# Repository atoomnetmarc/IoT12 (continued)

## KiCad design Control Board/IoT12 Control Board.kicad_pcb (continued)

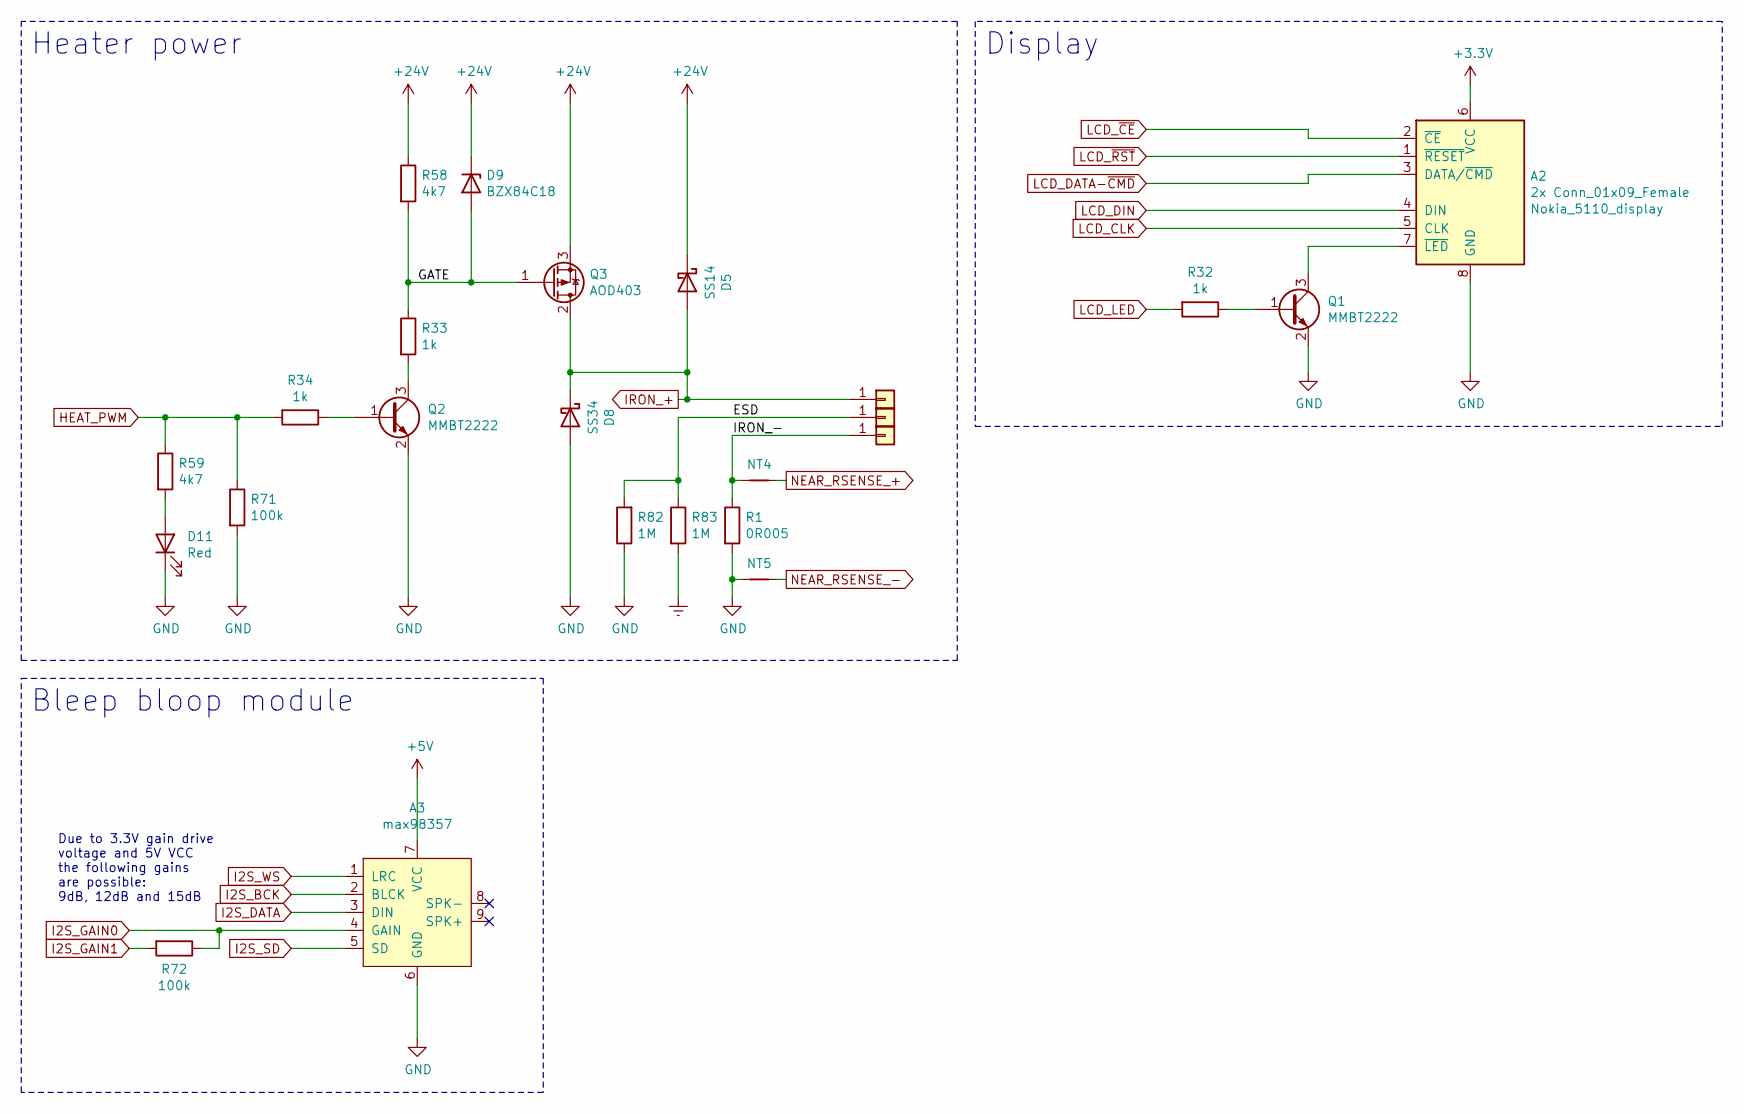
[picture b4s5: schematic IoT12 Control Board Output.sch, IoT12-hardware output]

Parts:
A2: 2x Conn_01x09_Female; Nokia_5110_display_module
A3: max98357
D5: SS14; D_SMA
D8: SS34; D_SMA
D9: BZX84C18; D_SOT-23_ANK
D11: Red; LED_0805_2012Metric_Pad1.15x1.40mm_HandSolder
J3, J4, J5: TestPoint_THTPad_D2.0mm_Drill1.0mm
NT4, NT5: NetTie-2_SMD_Pad0.25mm
Q1, Q2: MMBT2222; SOT-23
Q3: AOD403; TO-252-2
R1: 0R005; R_2512_6332Metric_Pad1.52x3.35mm_HandSolder
R32, R33, R34: 1k; R_0805_2012Metric_Pad1.20x1.40mm_HandSolder
R58, R59: 4k7; R_0805_2012Metric_Pad1.20x1.40mm_HandSolder
R71, R72: 100k; R_0805_2012Metric_Pad1.20x1.40mm_HandSolder
R82, R83: 1M; R_0805_2012Metric_Pad1.20x1.40mm_HandSolder

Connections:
+5V: A3.7 (VCC); also elsewhere on the board
+24V: D5.1 (K), D9.1 (K), Q3.3 (S), R58.1; also elsewhere on the board
/Output/ESD: J3.1, R82.2, R83.1
/Output/GATE: D9.2 (A), Q3.1 (G), R33.1, R58.2
/Output/IRON_-: J4.1, NT4.1, R1.1
Earth: R83.2; also elsewhere on the board
GND: A2.8 (GND), A3.6 (GND), D8.2 (A), D11.1 (K), NT5.1, Q1.2 (E), Q2.2 (E), R1.2, R71.2, R82.1; also elsewhere on the board
HEAT_PWM: R34.2, R59.1, R71.1; also elsewhere on the board
I2S_BCK: A3.2 (BLCK); also elsewhere on the board
I2S_DATA: A3.3 (DIN); also elsewhere on the board
I2S_GAIN0: A3.4 (GAIN), R72.1; also elsewhere on the board
I2S_GAIN1: R72.2; also elsewhere on the board
I2S_SD: A3.5 (SD); also elsewhere on the board
I2S_WS: A3.1 (LRC); also elsewhere on the board
IRON_+: D5.2 (A), D8.1 (K), J5.1, Q3.2 (D); also elsewhere on the board
LCD_CLK: A2.5 (CLK); also elsewhere on the board
LCD_DATA-~CMD: A2.3 (DATA/~CMD); also elsewhere on the board
LCD_DIN: A2.4 (DIN); also elsewhere on the board
LCD_LED: R32.2; also elsewhere on the board
LCD_~CE: A2.2 (~CE); also elsewhere on the board
LCD_~RST: A2.1 (~RESET); also elsewhere on the board
NEAR_RSENSE_+: NT4.2; also elsewhere on the board
NEAR_RSENSE_-: NT5.2; also elsewhere on the board
unnamed: A2.7 (~LED), Q1.3 (C)
unnamed: D11.2 (A), R59.2
unnamed: Q1.1 (B), R32.1
unnamed: Q2.1 (B), R34.1
unnamed: Q2.3 (C), R33.2

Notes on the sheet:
Display
Heater power
Bleep bloop module
Due to 3.3V gain drive voltage and 5V VCC the following gains are possible: 9dB, 12dB and 15dB

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
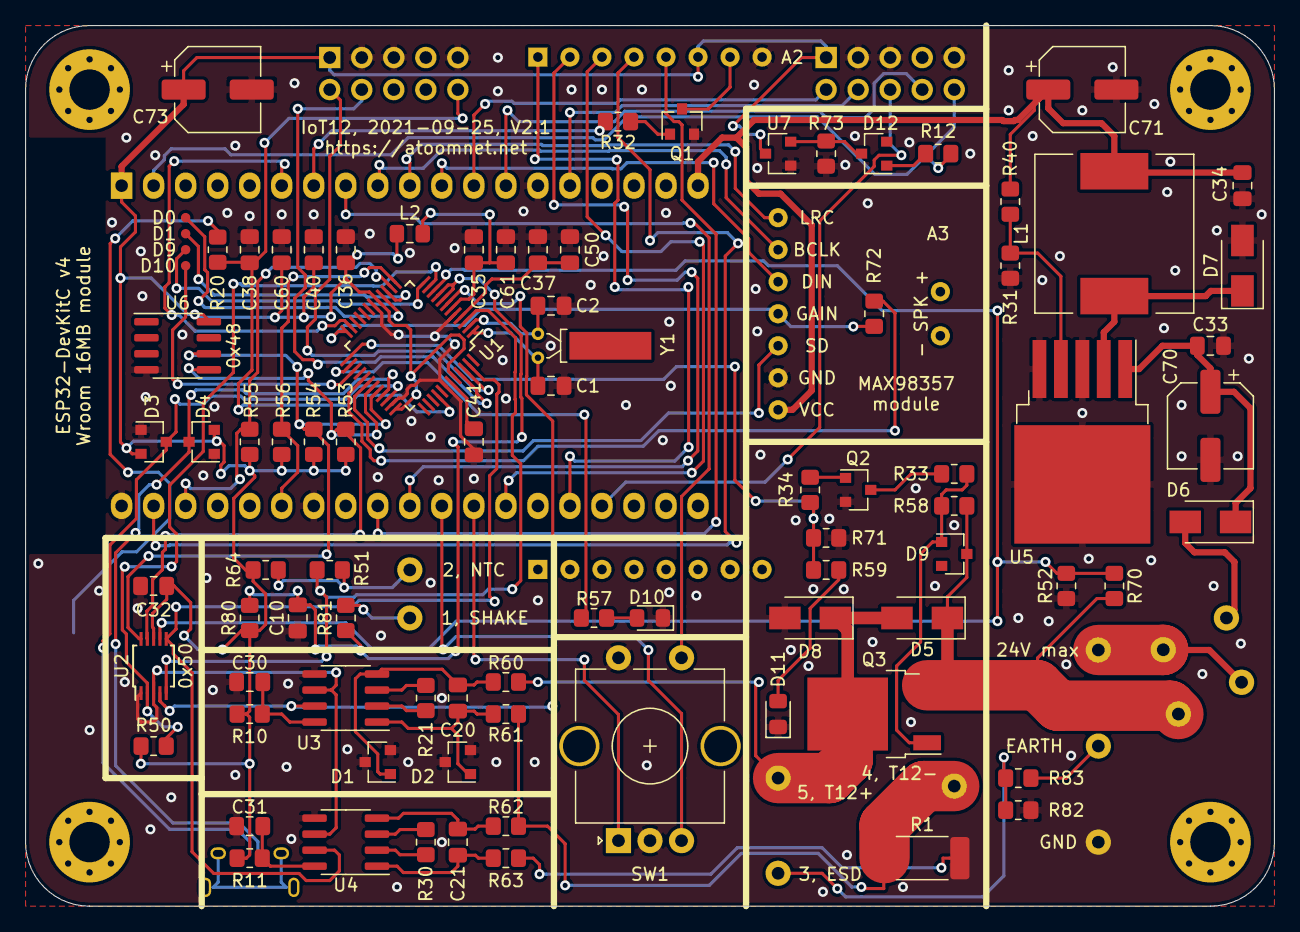
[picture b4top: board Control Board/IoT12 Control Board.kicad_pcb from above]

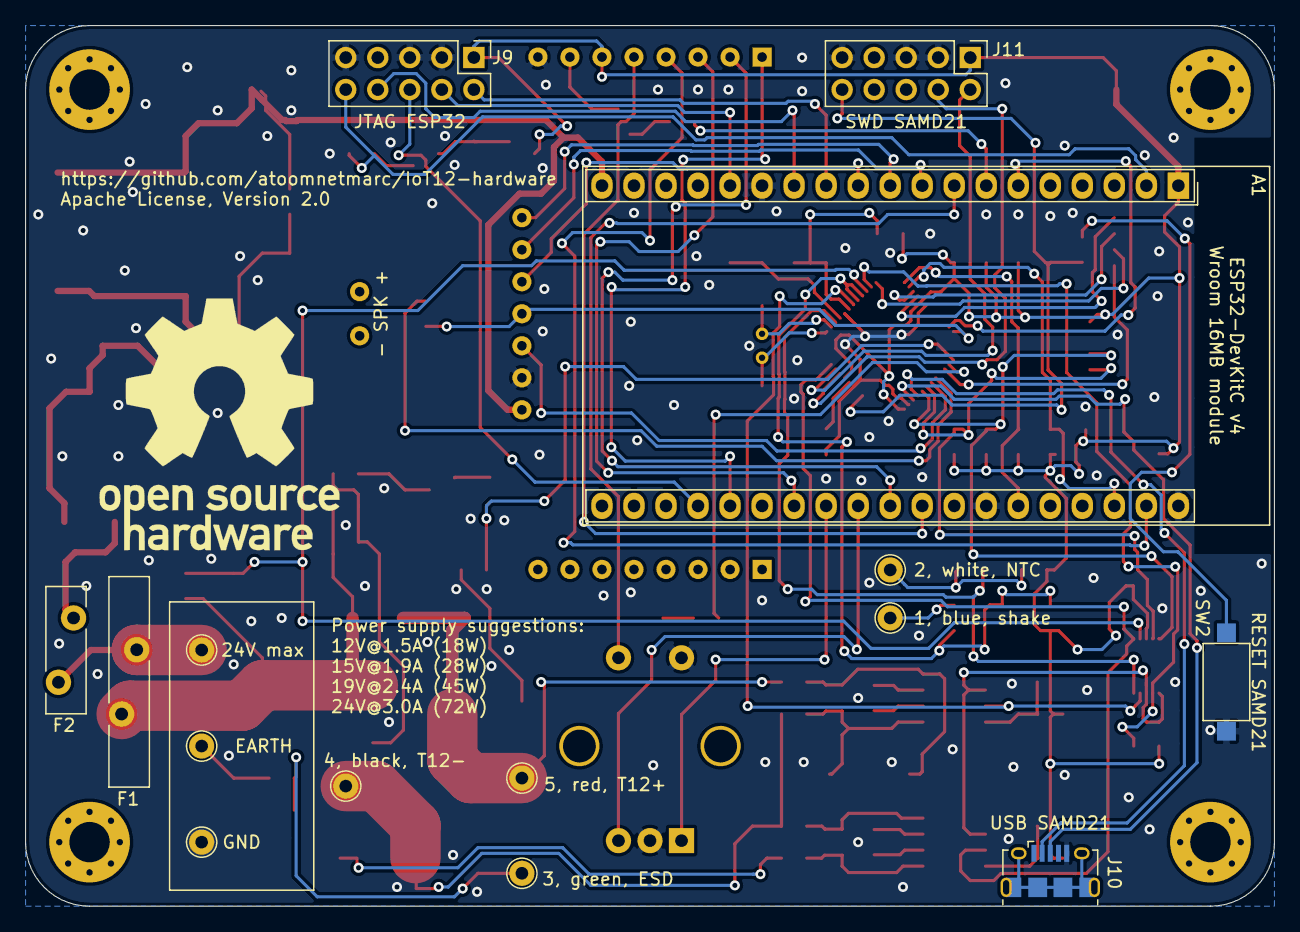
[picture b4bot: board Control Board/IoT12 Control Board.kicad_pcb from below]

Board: 2 copper layers, 99.1 x 69.8 mm, 111 parts (15 on the bottom side), 85 nets.

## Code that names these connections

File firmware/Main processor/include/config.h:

/*
 *
 * Copyright Marc Ketel
 * SPDX-License-Identifier: Apache-2.0
 *
 */

#pragma once

#define PIN_HEAT_INT 35

#define PIN_I2S_CLK   25
#define PIN_I2S_WS    26
#define PIN_I2S_DATA  27
#define PIN_I2S_SD    33
#define PIN_I2S_GAIN0 13
#define PIN_I2S_GAIN1 14

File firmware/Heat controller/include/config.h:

/*
 *
 * Copyright Marc Ketel
 * SPDX-License-Identifier: Apache-2.0
 *
 */

#pragma once

#include <Arduino.h>

#define PIN_HEAT_PWM  (10u)
#define PIN_24V_ON    (9u)
#define PIN_ADC_READY (8u)
#define PIN_HEAT_INT  (4u)
#define PIN_FLASH_CS  (6u)
#define PIN_SHAKE     A3

#define PIN_INTERNAL_ADC_NTC          PIN_A0
#define PIN_INTERNAL_ADC_TEMP         PIN_A1
#define PIN_INTERNAL_ADC_VIN          PIN_A4
#define PIN_INTERNAL_ADC_IRON_CURRENT PIN_A5

#define AIN_EXTERNAL_ADC_TEMP         (0u)
#define AIN_EXTERNAL_ADC_NTC          (1u)
#define AIN_EXTERNAL_ADC_IRON_CURRENT (2u)
#define AIN_EXTERNAL_ADC_VIN          (3u)

#define I2C_ADDRESS_ADS1115 0x48

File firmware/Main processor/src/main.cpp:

/*
 *
 * Copyright Marc Ketel
 * SPDX-License-Identifier: Apache-2.0
 *
 */

#include <esp32-hal-cpu.h>

#include <Wire.h>

#include <IoAbstraction.h>
#include <TaskManagerIO.h>

#include "HeatController.h"
#include "config.h"
#include "display.h"
#include "main.h"
#include "webserverc.h"
#include "wific.h"

volatile int encoderValue = 30;
void onEncoderChange(int newValue) {
    RequestDrawDisplay();

    if (newValue > 0 && encoderValue < 600) {
        encoderValue += 5;
    }

    if (newValue < 0 && encoderValue > -10) {
        encoderValue -= 5;
    }

    /*
    if (newValue < 0)
        Serial.println("down");
    else
        Serial.println("up");
    */

    float celsius = encoderValue;

    HeatController.setTargetTemperature(celsius + 273.15f);
}

void onSpinwheelClicked(uint8_t pin, bool heldDown) {
    Serial.print("Button pressed ");
    Serial.println(heldDown ? "Held" : "Pressed");

    /*
  u8g2.beginSimple();
  u8g2.setPowerSave(0);
  */

    if (heldDown == false) {
        HEATER_STATE state = HeatController.getHeaterState();
        if (state == HEATER_STATE::OFF) {
            HeatController.setHeaterState(HEATER_STATE::ON);
        } else {
            HeatController.setHeaterState(HEATER_STATE::OFF);
        }
    }

    /*
    SerialNumber_t sn = HeatController.getSerialNumber();
    Serial.println(String("Serial number heatcontroller: ") + String(sn.word0, HEX) + String(" ") + String(sn.word1, HEX) + String(" ") + String(sn.word2, HEX) + String(" ") + String(sn.word3, HEX) );

    uint16_t const1 = HeatController.getConst1();
    Serial.println(String("Const1 heatcontroller: 0x") + String(const1, HEX) );

    float const2 = HeatController.getConst2();
    Serial.println(String("Const2 heatcontroller: ") + String(const2, 6));
    */
}

void setup() {
    Wire.begin(SDA, SCL, 100000U);

    Serial.begin(115200);
    Serial.println(F("Booting"));

    setCpuFrequencyMhz(80);
    Serial.println(String(F("CPU freq: ")) + String(ESP.getCpuFreqMHz()) + String(F("MHz")));
    Serial.println(String(F("Flash size: ")) + String(ESP.getFlashChipSize() / 1024 / 1024) + String(F("MiB")));

    DisplaySetup();

    pinMode(PIN_ROT_A, PULLUP);
    pinMode(PIN_ROT_B, PULLUP);
    pinMode(PIN_ROT_SW, PULLUP);
    switches.initialiseInterrupt(ioUsingArduino(), true);
    switches.addSwitch(PIN_ROT_SW, onSpinwheelClicked);
    setupRotaryEncoderWithInterrupt(PIN_ROT_A, PIN_ROT_B, onEncoderChange);
    switches.changeEncoderPrecision(0, 0);

    WificSetup();

    pinMode(PIN_LCD_LED, OUTPUT);
    digitalWrite(PIN_LCD_LED, 1);

    if (HeatController.init() == false) {
        Serial.println(F("Heat controller not compatible"));
    }
    Serial.println(String(F("Heat controller version: ")) + HeatController.getFirmwareVersion());

    taskManager.scheduleFixedRate(
        200, [] {
            RequestDrawDisplay();
        },
        TIME_MILLIS);
}

void CriticalLoop() {
    HeatController.loop();
    taskManager.yieldForMicros(0);
    yield();
}

void loop() {
    CriticalLoop();
    taskManager.runLoop();

    WiFicLoop();
    WebservercLoop();
    DisplayLoop();
}

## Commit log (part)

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2021-02-06 Added license
2021-02-06 Knob1
2021-02-06 Inline stl renderer does not work for me.
2021-03-06 Changed to permissive license.
2021-03-14 Initial commit.
2021-03-17 Tune BOD33 fuse setting.
2021-03-27 Align.
2021-04-03 Changed most uint32_t types to float.
2021-04-03 Added register usage overview.
2021-04-04 Documented registers.
2021-04-04 Changed registers.
2021-04-04 Changed 0x08 from 16B to 4x uint32_t.
2021-04-04 Added 2 constants to test little-endian transfers.
2021-04-04 Updated register usage overview.
2021-04-25 First working version.
2021-09-12 Remove capacitor and resistor from usb shield.
2021-09-25 Minor change.
2021-09-25 Next attempt building case.
2021-09-25 PCB component placement change.
2021-09-26 Floating pcb supports do not work in real life.
2021-09-26 Enlarge hole for knob.
2021-09-26 Add LCD pin labels. Add testpoints heat controller.
2021-10-01 Progress building case.
2021-10-01 Lid stl.
2021-10-02 Next iteration after print.
2021-10-08 Add: this PCB is not safe to use.
2021-10-08 Add BOM and gerber files.
2021-10-21 Remove all lower power supply options.
2021-11-07 Add knob.
2021-11-15 Bump library and platforms versions
2021-11-17 Typo
2021-11-18 Refactor adc code
2021-11-20 .gitignore libreoffice
2021-11-20 Bump library and platform versions.
2021-11-20 Refactor heating logic.
2021-11-20 Switch to external ADC.
2021-11-21 Replace bang-bang with PID controller.
2021-11-21 Add thermocouple input offset compensation.
2021-11-22 Add copy hex and lss file
2021-11-23 Reference heat controller readme.md
2021-11-27 Move hardware files to subdirectory
2021-11-27 Move firmware files to subdirectory
2021-11-27 Move 3d files to subdirectory
2021-11-27 Update readme.md's now that 3 repositories are merge into one.
2022-01-28 Kicad 5 to 6 upgrade.
2022-02-04 Lib & platform update.
2022-03-04 Update dependencies.
2022-03-04 Measure current only on larger heat duty cycle.
2022-03-04 Update copyright year.
2022-08-22 Errata for PCB V2.1
2022-11-02 Open sch and brd, delete *.sch and *.brd, then save in Kicad 6.0.9 to resolve errors while saving.
2022-11-19 Start of next iteration.
2022-11-20 Ignore .zip
2022-12-06 Add display adapter assembly instructions.
2022-12-10 Add PDF. Enlarge F1 pad size.
2022-12-10 Make more room around F1.
2022-12-10 Add new revision Power Supply assembly instruction.
2022-12-10 Corrected footprint for INA826AID.
2022-12-10 Control board assembly instructions.
2022-12-10 Replace render with photo.
2022-12-10 Move changelog of control board to control board readme.
2022-12-11 Add start of assembly instuctions.
2023-05-16 Fix gerber directory.
2023-05-18 Clarify use of ESP32-WROOM-32E.
2023-09-24 Redesign 3d-printable case.
2023-09-24 Change hv-shield dimension.
2023-09-29 Change 3d design after first print.
2023-09-30 Next iteration on 3d design.
2025-06-17 Apply TLC. Make heat controller compile again.
2025-06-17 Apply TLC. Firmware is still for the old LCD version.
2026-01-23 Add CONTRIBUTING.md
